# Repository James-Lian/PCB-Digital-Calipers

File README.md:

# PCB Digital Calipers
A PCB project to build DIY digital calipers using custom capacitive sensors and a Seeed Studio Xiao RP2040.
<br>
Stardance Project Tracker (devlogs): [https://stardance.hackclub.com/projects/32382](https://stardance.hackclub.com/projects/32382)

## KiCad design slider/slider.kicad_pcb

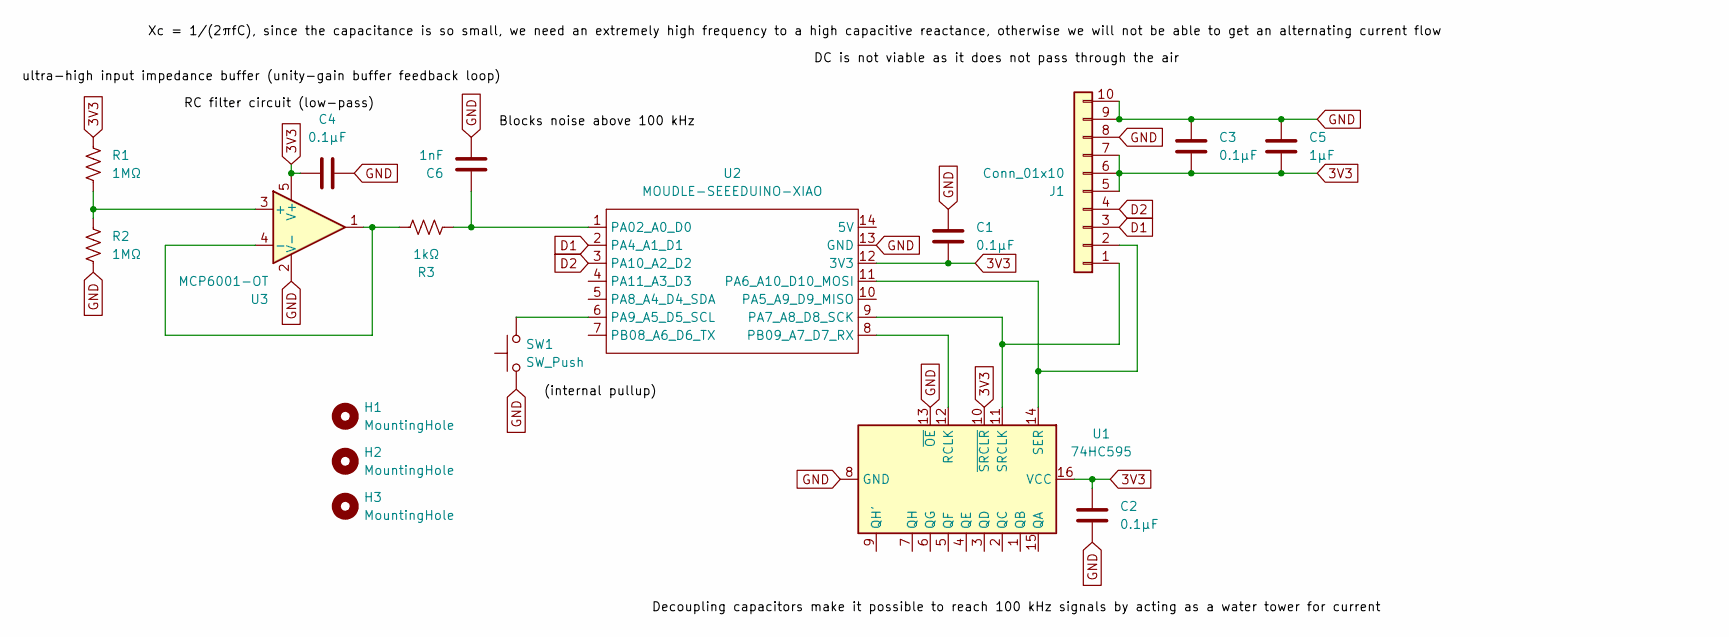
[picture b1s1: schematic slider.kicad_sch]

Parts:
C1, C2, C3, C4: 0.1µF; C_0805_2012Metric
C5: 1µF; C_0805_2012Metric
C6: 1nF; C_0805_2012Metric
H1, H2, H3: MountingHole; MountingHole_3.2mm_M3
J1: Conn_01x10; Hirose_FH12-10S-0.5SH_1x10-1MP_P0.50mm_Horizontal
R1, R2: 1MΩ; R_Axial_DIN0207_L6.3mm_D2.5mm_P7.62mm_Horizontal
R3: 1kΩ; R_Axial_DIN0207_L6.3mm_D2.5mm_P7.62mm_Horizontal
SW1: SW_Push; SW_SPST_PTS645Sx43SMTR92
U1: 74HC595; TSSOP-16_4.4x5mm_P0.65mm
U2: MOUDLE-SEEEDUINO-XIAO; XIAO-Generic-Hybrid-14P-2.54-21X17.8MM
U3: MCP6001-OT; SOT-23-5

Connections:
3V3: C1.2, C2.1, C3.1, C4.1, C5.2, J1.5, J1.6, J1.7, R1.2, U1.10 (~SRCLR), U1.16 (VCC), U2.12 (3V3), U3.5 (V+)
D1: J1.3, U2.2 (PA4_A1_D1)
D2: J1.4, U2.3 (PA10_A2_D2)
GND: C1.1, C2.2, C3.2, C4.2, C5.1, C6.2, J1.8, J1.9, J1.10, R2.1, SW1.1, U1.8 (GND), U1.13 (~OE), U2.13 (GND), U3.2 (V-)
unnamed: J1.1, U1.11 (SRCLK), U2.9 (PA7_A8_D8_SCK)
unnamed: J1.2, U1.14 (SER), U2.11 (PA6_A10_D10_MOSI)
unnamed: U1.12 (RCLK), U2.8 (PB09_A7_D7_RX)
unnamed: C6.1, R3.1, U2.1 (PA02_A0_D0)
unnamed: SW1.2, U2.6 (PA9_A5_D5_SCL)
unnamed: R1.1, R2.2, U3.3 (+)
unnamed: R3.2, U3.1, U3.4 (-)

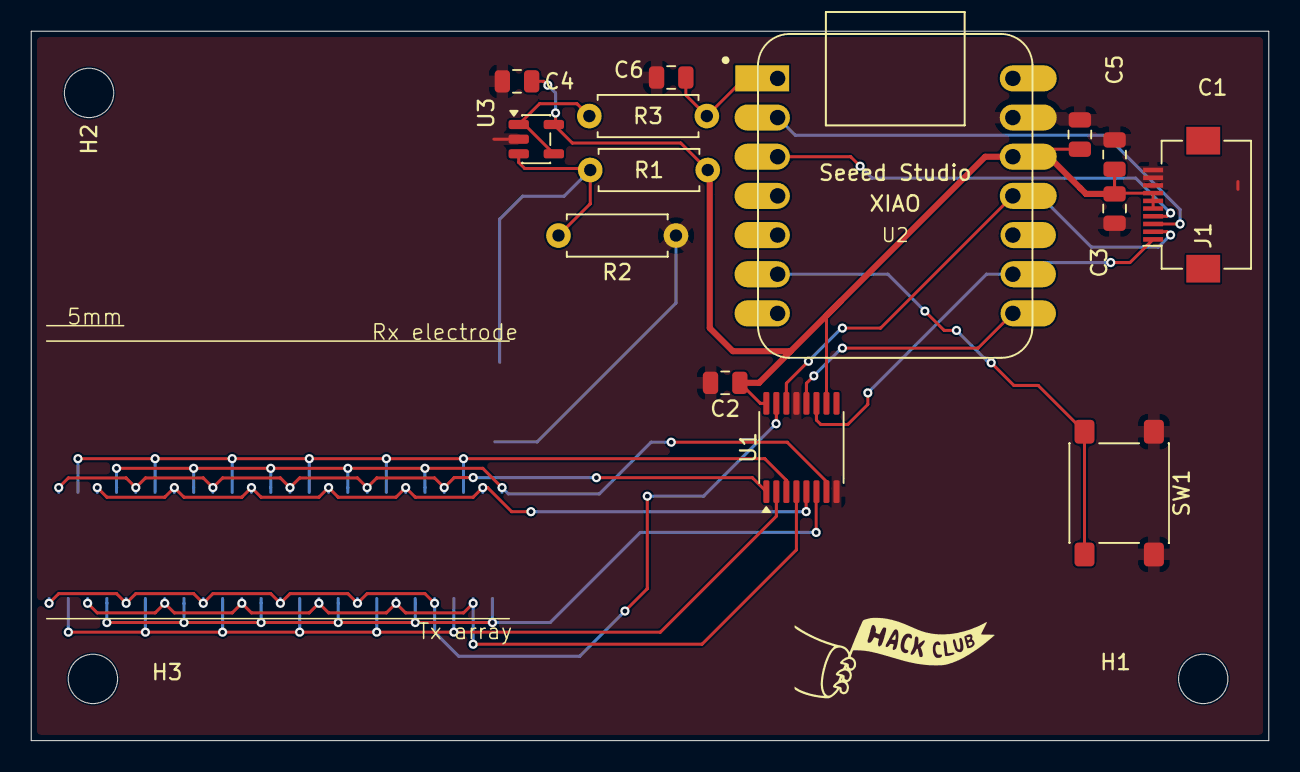
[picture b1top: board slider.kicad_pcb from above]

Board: 2 copper layers, 80.2 x 46.0 mm, 17 parts (0 on the bottom side), 11 nets.

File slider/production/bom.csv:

Designator,Footprint,Quantity,Value,LCSC Part #
"C1, C2, C3, C4",0805,4,0.1µF,
C5,0805,1,1µF,
C6,0805,1,1nF,
J1,Hirose_FH12-10S-0.5SH_1x10-1MP_P0.50mm_Horizontal,1,Conn_01x10,
"R1, R2",R_Axial_DIN0207_L6.3mm_D2.5mm_P7.62mm_Horizontal,2,1MΩ,
R3,R_Axial_DIN0207_L6.3mm_D2.5mm_P7.62mm_Horizontal,1,1kΩ,
SW1,SW_SPST_PTS645Sx43SMTR92,1,SW_Push,
U1,TSSOP-16_4.4x5mm_P0.65mm,1,74HC595,
U2,XIAO-Generic-Hybrid-14P-2.54-21X17.8MM,1,MOUDLE-SEEEDUINO-XIAO,
U3,SOT-23-5,1,MCP6001-OT,
